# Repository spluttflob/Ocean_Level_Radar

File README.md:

This project aims to create simple and inexpensive designs for measuring 
ocean level from piers, pilings, trees, or other relatively fixed
locations above the water.  THe measurements are to be taken quickly enough
that ocean waves and perhaps wind chop can be resolved. 
Ocean Science Hippies will use these measurements to better understand the 
effects of tides, waves, tsunamis, sea level rise, and other ocean phenomena 
on the coastal environment. 

## Hardware

The custom circuit board design currently used is in `hardware`. 

Mechanical part designs, including radar antennas and lenses, are currently 
being developed and will be added to this repository if and when we figure out
what on Earth we're doing. 

### Power

The current (2026 January) hardware versions may be powered by connecting the
ESP32 to a laptop through a USB cable, **or** by supplying the system with 
5 volts DC through the water resistant connector on the box. 

If a laptop cannot supply enough current through its USB port, the ESP32 may
reboot due to low supply voltage (it says `brownout detected`.)  Usually, 
rebooting a couple of times causes it to come to life; if that doesn't work, 
try another laptop and/or a powered USB hub. 

<span color="red">Only one source of power should be used at a time; **do not** 
connect the ESP32 Feather to a PC while DC power is being supplied through the 
waterproof connector.</span>

## Firmware

The software currently being developed uses a MicroPython program running on an
ESP32 as the overall controller, data logging, and network interface computer.
There is an STM32 microcontroller in the XM125 radar module which runs it own
software which is written in C. 

### ESP32 Firmware

There are two versions of the software which have been developed. The first
version is written in C++, and the second (and currently being worked on) 
version is in MicroPython.

#### C++

The C++ ESP32 firmware is in the `WaterSense_Radar_JJH` directory. 
After cloning this repository, open the `WaterSense_Radar_JJH` directory in a
VSCode/PlatformIO workspace and you should be able to compile and run the
ESP32 firmware. It requires custom firmware to be running on the STM32 in
the XM125 module.

#### MicroPython

For rapid development and testing, MicroPython firmware is provided in the
`MicroPython` folder.  MicroPython for the ESP32 can be downloaded from:  
<https://micropython.org/download/ESP32_GENERIC/>  
The latest release of the `ESP32_GENERIC` software is recommended for our
Feather circuit boards. 

With MicroPython installed on the ESP32, all the Python source files should 
be copied to the root directory of the ESP32's MicroPython filesystem, and 
`radar.cfg` should be copied to the root directory of the ESP32 file
system. Configuration of the system for use at specific sites may require 
editing of `main.py` and `task_mqtt.py`. The main Python file is edited to 
disable unneeded tasks; for example, the MQTT task should be turned off 
(just comment out the `asyncio.create_task()` line) at sites where WiFi 
access and AC power are not available. The radar's range, frequency of data 
collection, and similar configurations are set in `radar.cfg`. 

##### MicroPython File List

The following files need to be uploaded to the root directory of the ESP32's
MicroPython filesystem:

* `as_GPS.py` -- The asyncio GPS file from 
  <https://github.com/peterhinch/micropython-async/tree/master>
  or use the older, unmaintained copy here.
  
* `as_xm125_distance.py` -- From this repository.

* `main.py` -- From this repository.

* `mqtt_as.py` -- The asyncio MQTT client from
  <https://github.com/peterhinch/micropython-mqtt>
  or use the older, unmaintained copy here

* `pcf8523.py` -- Driver for the PCF8523 real-time clock on the Adalogger.
  Modified from others' work; use the copy here.
  
* `queue.py` -- From the standard MicroPython queues at 
  <https://github.com/peterhinch/micropython-async/tree/master>
  again, with an old local copy here for convenience.

* `task_gps.py` -- GPS task file from this repository.

* `task_mqtt.py` -- MQTT task (used if you have AC and WiFi) from this repository.

* `task_sd_card.py` -- SD card task from this repository.

* `radar.cfg` -- The configuration file for each site, put on the SD card.

#### Configuration with `radar.cfg`

The configuration file is a regular text file saved on the data logging SD card.
A typical configuration file might look as follows (for 2025-Dec version of the 
software; configurations are expected to change as the software is improved):
```txt
# Configuration file for Bogan Radar

Site Name:           My_Bench   # Name of site; should be one word (no spaces)
Beginning Distance:  2.0        # Beginning distance (m)
Ending Distance:     8.0        # Ending distance (m)
Sensitivity:         500        # Peak threshold sensitivity
Time Per Point:      5.0        # Time between data points (seconds)
Awake Time:          0.0        # Time taking data, sec., or 0.0 for always awake
Cycle Time:          0.0        # Total on-off cycle time, or 0.0 for always awake
```

_With changes to the value of `SD_DIR` in `task_sd_card.py`, the configuration
file could be saved in the ESP32's built-in flash; this would make reconfiguration 
a little harder but protect the configuration from SD card corruption due to power 
loss, somebody hot swapping the card (bad idea), etc._

If data is sent through MQTT, the MQTT topic is made by appending the site name
from the configuration file to `bogan_radar/`. 

### STM32 on XM125 Firmware

The STM32 microcontroller on the XM125 radar can be given a custom program to
optimize the radar module for our use. We have two setups available:

* When using the MicroPython firmware on the ESP32, the XM125's STM32 must be
  flashed with Acconeer's standard distance measurement application.
  The Acconeer software is available from:  
  <https://developer.acconeer.com/home/a121-docs-software/xm125-xe125/>  
  (You have to enroll with a developer account, but at least it's free to do 
  so.)

* When using the C++ firmware from directory `WaterSense_Radar_JJH` for the 
  ESP32, the source code for the STM32 microcontroller in the XM125 radar 
  module from subdirectory `xm125` must be compiled and flashed to the XM125.
  Compiling the XM125 STM32 code is a bit of a hassle, so we can use a binary 
  copy of the last working code.
  
* It's convenient to use an ST-Link2 programmer to flash the STM32 code to the 
  radar module. There is an ST-Link2 compatible 6-pin programming header near
  the screw terminal on the main circuit board, and there are two pushbuttons
  on the board to reset the STM32 and to put the STM32 in bootloader mode if 
  needed. 

## PC Software

### The _Acconeer Exploration Tool_

This handy application consists of a firmware package and a PC application.
Although it's designed to be run on an official Acconeer development board, the
Exploration Tool can also be run on our boards.

Instructions for setting up the STM32 firmware and Python PC software are at
<https://github.com/acconeer/acconeer-python-exploration>.  Follow Acconeer's 
instructions **with the following exceptions:**

* We usually use leftover ST-Link2 programmers (from old STM32 Nucleo&trade; boards) 
  instead of fussing with DFU programming.  The 6-pin ST-Link2 header next to 
  the power and battery connectors is connected directly to the 6-pin `SWD` (CN4) 
  connector on the ST-Link2, matching the ends marked with dots or triangles. 
  The STM32 Cube Programmer&trade; is a convenient way to flash the binary file
  for the firmware to the STM32. 

* To use our boards with the Exploration Tool, first remove the ESP32 Feather 
  board, any FeatherWing accsesory boards, and the GPS module from the main radar 
  circuit board. Leaving the GPS antenna in place, if present, is OK. 
  Then attach a connector (header pins or sockets) to the three-pin header pad
  marked `STM32 UART0` in the area where the GPS board sits.  Connect a USB to
  RS-232 serial adapter to STM32 UART0 pins, remembering the annoying RS-232 
  standard where RXD of one device must connect to TXD of the other. 
  If you're a civil, environmental, or mechanical engineer: Don't forget the 
  ground wire!  `:)`
  The Exploration Tool should now be able to connect to the XM125 as if the
  XM125 were on the official evaluation board. 

<!-- 
* Use ST-Link to load firmware
* Connect USB-Serial to ST's UART
* Set up Exploration Tool on PC
--> 

### Plotting MicroPython Data

If MicroPython is used, data will be saved in a Semicolon And Comma Separated
Variable (`.sacsv`) format. Some simple programs to plot data in this form are
being developed and can be found in the `CPython` directory. 

An older plotting program (look for lower numbers) uses data in a format 
without the date on each reading; this has caused some inconvenience, so newer
data is saved will a full datetime on every reading, and newer CPython scripts
with higher numbers in the file names use the newer format. 

### Plotting C++ Firmware Data

Some more fully Python developed programs to analyze data from the C++ firmware 
are in the `ESP32_to_Python_GUI` directory. 

It is our intention to merge the capabilities of the CPython programs from
the `CPython` and `ESP32_to_Python_GUI` directories to create especially 
convenient and flexible data analysis and plotting applications. 

## References

* A Masters thesis utilizing ultrasonic rather than radar sensors which gives
  some perspective to the project:  
  <https://digitalcommons.calpoly.edu/theses/2745/>

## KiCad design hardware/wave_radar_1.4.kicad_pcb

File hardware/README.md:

# Bogan Radar Hardware Notes

**Version 1.4 (Still in alpha)**

This newer board is simpler and easier to assemble than V1.3.  All the SMD parts
are on one side of the board, so the SMDs can be soldered on first; a hot plate
works pretty well for this.  After the SMDs are in place, the through-hole parts 
can be attached to the other side.  The assembly of the board to the radar
antenna and installation in an enclosure are the same for both boards. 

**Version 1.3 (Obsolete; do not use)**

_**NOTE:** The 1.3 board version has not performed well enough in testing and is
considered obsolete. Newer boards are being prepared. The process of installing
the newer boards will be the same as that of installing older boards._

The current design uses the following bits:

* An Acconeer&trade; XM125 radar mounted to the bottom of a circuit board, with
  headers for many of the XM125 pins broken out to through holes on the board

* An Adalogger&trade; Featherwing for its SD card and battery backed up 
  real-time clock, mounted in a socket atop the board using stacking headers

* An ESP32 Feather board (EZSBC made boards preferred) mounted atop the 
  Adalogger
  
* A generic GPS receiver atop the circuit board

* A LiPo battery charging circuit built into the Feather board

The radar system is enclosed in a generic waterproof junction box. 
The board is mounted atop a horn-type millimeter-wave antenna that is attached
to the box with a waterproof seal.  The system is watertight so that it has a
chance to survive when deployed just above the ocean. 

_Note from testing: The enclosure shown has been tested in and survived 
several rainstorms, though a small amount of water was found in the bottom of
the box after about 6 weeks and several storms._

## Board V1.3 Hacks (legacy; use newer boards)

The design of the system has changed since a batch of the Version 1.3 boards
was manufactured, so there have been some hacks made involving jumper wires.
Please see [HACKS_1.3](HACKS_1.3.md) for details.

## RADAR Antenna

The horn antenna is a simple cylindrical design, manufactured mostly using a
lathe:

There are other antennas available such as plastic lenses. These may work well
also, and antenna testing and comparison are ongoing.

## Mounting in Enclosure

The branding of a typical enclosure is shown below.  This is not an endorsement
of this particular enclosure above others; it's just something we've tried:

The antenna is mounted in the bottom of the box. A 1 inch hole is cut for the
antenna and the antenna is pushed in from the outside. We have had good results
using a step drill to make the hole.  Sealant is applied to
the flat mounting face of the antenna to prevent water ingress, and a couple of 
\#6-32 screws are tapped into the mounting face of the antenna to secure it to 
the box:

A 3D printed board mounting piece is attached to the upper side of the antenna 
to mount the circuit board. The end of the antenna must be flush with the slot
in the face of the board mount, as shown below using a ruler to verify that the
board mount is at the correct height. It's a little hard to see in the photo,
but the edge of the ruler is down in the slot, _not_ up on the faces of the
board mount that contact the board. This is critical because the XM125 sensor
will be in that slot when the board is mounted:

The board attaches to its mount with four annoyingly tiny screws. Ensure that
nobody sneezes to prevent losing the screws.  After the board is mounted, the
Featherwing, ESP32, and GPS can be inserted in their sockets and the electrical
power connection (see below) hooked up. 

The ESP32 Feather and Adalogger boards are stacked onto the Feather connectors
on the board in the usual way. Depending on the type of GPS module used, one
may need to mount the GPS antenna separately from the GPS module board.  If so,
the antenna can be mounted to the area marked `GPS Antenna Pad` on the board
with some double-sided foam tape. 
It is recommended to mount the GPS antenna so that the board mounting screw is
easily accessible with a screwdriver, as the need to remove the board for
updates or repairs is all but guaranteed in a research project. 

## Electrical Power Connection

For most uses, electricity must be supplied to the radar system from outside, 
either a solar panel or 5 volt wall plug adapter. _**Note:** The adapter should
be rated to produce 5.0 to 5.2 volts at around 1 amp. EZSBC boards are
designed to be supplied from 5 volt USB supplies and rated to handle up to 5.5
volts._  The power connection must be watertight.  In an experimental setup, we
have used an inexpensive waterproof automotive style connector glued into a hole
in the side of the box. 

## Radar Antenna Cover

This is an area of ongoing research. The radar may have an optimally tight beam
if a plastic phase corrector is attached across the bottom (wide) opening of
the horn antenna, but for initial testing we're trying polypropylene and
polyethylene disks made from various containers. The cover's ideal width which 
minimizes reflections of the 60GHz signal depends on the material used. 
The Interwebs seem to say that a 1.5mm (about 1/16") sheet of polypropylene 
would make a good cover. Disks of UHMW polyethylene (we think) cut from a
Tupperware&trade; bowl lid saved from a dumpster seem to work pretty well too.
More will be posted when we have conducted more experiments. 

Remember that the cover must be attached to the end of the horn with a 
watertight connection to protect the sensor from rain, waves, spray, and
errant organisms. A version of the aluminum horn antenna which has a threaded
end, combined with a threaded PVC ring that holds a cover firmly against the
end of the antenna, seems to work well.  We may use a bit of caulk or pipe
dope to ensure a good seal.

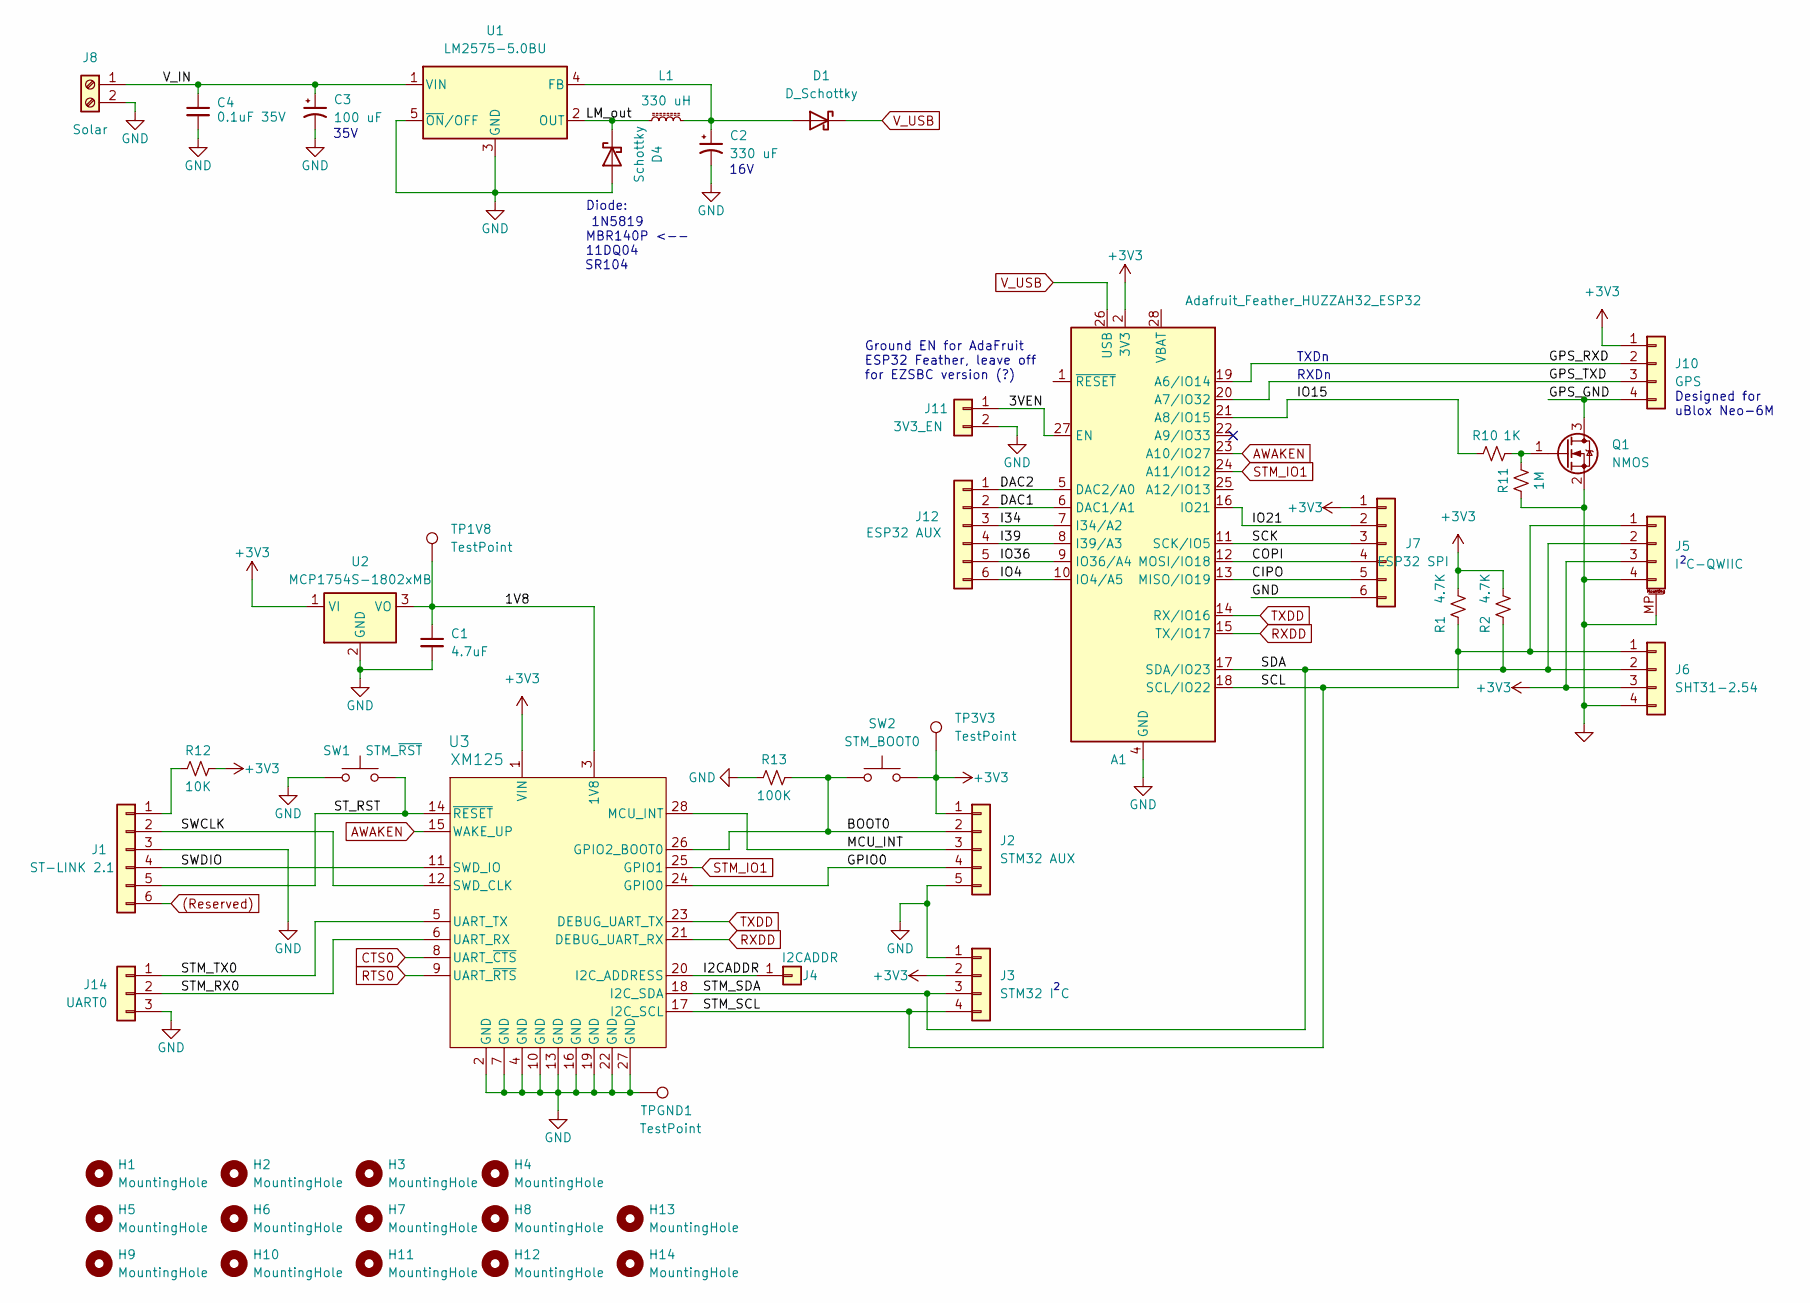
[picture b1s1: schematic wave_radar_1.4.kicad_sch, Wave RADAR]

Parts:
A1: Adafruit_Feather_HUZZAH32_ESP32; Adafruit_Feather
C1: 4.7uF; C_0805_2012Metric
C2: 330 uF; CP_Radial_D8.0mm_P3.50mm
C3: 100 uF; CP_Radial_D8.0mm_P3.50mm
C4: 0.1uF 35V; C_0805_2012Metric
D1: D_Schottky; D_1206_3216Metric
D4: Schottky; D_1206_3216Metric
H1, H2, H3, H4, H5, H6, H7, H8, H9, H10, H11, H12, H13, H14: MountingHole; MountingHole_2.7mm
J1: ST-LINK 2.1; PinHeader_1x06_P2.54mm_Vertical
J2: STM32 AUX; PinHeader_1x05_P2.54mm_Vertical
J3: STM32 I C; PinHeader_1x04_P2.54mm_Vertical
J4: I2CADDR; PinHeader_1x01_P2.54mm_Vertical
J5: I C-QWIIC; JST_SH_BM04B-SRSS-TB_1x04-1MP_P1.00mm_Vertical
J6: SHT31-2.54; PinHeader_1x04_P2.54mm_Vertical
J7: ESP32 SPI; PinHeader_1x06_P2.54mm_Vertical
J8: Solar; TerminalBlock_Phoenix_MPT-0,5-2-2.54_1x02_P2.54mm_Horizontal
J10: GPS; PinSocket_1x04_P2.54mm_Vertical
J11: 3V3_EN; PinHeader_1x02_P2.54mm_Vertical
J12: ESP32 AUX; PinHeader_1x06_P2.54mm_Vertical
J14: UART0; PinHeader_1x03_P2.54mm_Vertical
L1: 330 uH; Inductors for LM2575, Pulse PE-xxxxx
Q1: NMOS; SOT-23
R1, R2: 4.7K; R_0805_2012Metric
R10: 1K; R_0805_2012Metric
R11: 1M; R_0805_2012Metric
R12: 10K; R_0805_2012Metric
R13: 100K; R_0805_2012Metric
SW1: STM_~{RST}; SW_PUSH_1P1T_6x3.5mm_H4.3_APEM_MJTP1243
SW2: STM_BOOT0; SW_PUSH_1P1T_6x3.5mm_H4.3_APEM_MJTP1243
TP1V8, TP3V3: TestPoint; TestPoint_Loop_D2.50mm_Drill1.0mm
TPGND1: TestPoint; TestPoint_Loop_D2.50mm_Drill1.0mm
U1: LM2575-5.0BU; TO-263-5_TabPin3
U2: MCP1754S-1802xMB; SOT-223-3_TabPin2
U3: XM125; XM125_ACC

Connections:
(Reserved): J1.6
+3V3: A1.2 (3V3), J2.1, J3.2, J5.3, J6.3, J7.1, J10.1, R1.2, R2.2, R12.2, SW2.2, TP3V3.1, U2.1 (VI), U3.1 (VIN)
/1V8: C1.1, TP1V8.1, U2.3 (VO), U3.3 (1V8)
/3VEN: A1.27 (EN), J11.1
/BOOT0: J2.2, R13.2, SW2.1, U3.26 (GPIO2_BOOT0)
/CIPO: A1.13 (MISO/IO19), J7.5
/COPI: A1.12 (MOSI/IO18), J7.4
/DAC1: A1.6 (DAC1/A1), J12.2
/DAC2: A1.5 (DAC2/A0), J12.1
/GPIO0: J2.4, U3.24 (GPIO0)
/GPS_GND: J10.4, Q1.3 (D)
/GPS_RXD: A1.19 (A6/IO14), J10.2
/GPS_TXD: A1.20 (A7/IO32), J10.3
/I2CADDR: J4.1, U3.20 (I2C_ADDRESS)
/I34: A1.7 (I34/A2), J12.3
/I39: A1.8 (I39/A3), J12.4
/IO4: A1.10 (IO4/A5), J12.6
/IO15: A1.21 (A8/IO15), R10.1
/IO21: A1.16 (IO21), J7.2
/IO36: A1.9 (IO36/A4), J12.5
/LM_out: D4.1 (K), L1.1, U1.2 (OUT)
/MCU_INT: J2.3, U3.28 (MCU_INT)
/SCK: A1.11 (SCK/IO5), J7.3
/SCL: A1.18 (SCL/IO22), J3.4, J5.1, J6.1, R1.1, U3.17 (I2C_SCL)
/SDA: A1.17 (SDA/IO23), J3.3, J5.2, J6.2, R2.1, U3.18 (I2C_SDA)
/STM_RX0: J14.2, U3.6 (UART_RX)
/STM_TX0: J14.1, U3.5 (UART_TX)
/ST_RST: J1.5, SW1.1, U3.14 (~RESET)
/SWCLK: J1.2, U3.12 (SWD_CLK)
/SWDIO: J1.4, U3.11 (SWD_IO)
/V_IN: C3.1, C4.1, J8.1, U1.1 (VIN)
AWAKEN: A1.23 (A10/IO27), U3.15 (WAKE_UP)
CTS0: U3.8 (UART_~CTS)
GND: A1.4 (GND), C1.2, C2.2, C3.2, C4.2, D4.2 (A), J1.3, J2.5, J3.1, J5.4, J5.MP (MountPin), J6.4, J7.6, J8.2, J11.2, J14.3, Q1.2 (S), R11.1, R13.1, SW1.2, TPGND1.1, U1.3 (GND), U1.5 (~ON/OFF), U2.2 (GND), U3.2 (GND), U3.4 (GND), U3.7 (GND), U3.10 (GND), U3.13 (GND), U3.16 (GND), U3.19 (GND), U3.22 (GND), U3.27 (GND)
unnamed: C2.1, D1.2 (A), L1.2, U1.4 (FB)
unnamed: J1.1, R12.1
unnamed: Q1.1 (G), R10.2, R11.2
RTS0: U3.9 (UART_~RTS)
RXDD: A1.15 (TX/IO17), U3.21 (DEBUG_UART_RX)
STM_IO1: A1.24 (A11/IO12), U3.25 (GPIO1)
TXDD: A1.14 (RX/IO16), U3.23 (DEBUG_UART_TX)
V_USB: A1.26 (USB), D1.1 (K)

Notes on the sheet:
SR104
1N5819
35V
Ground EN for AdaFruit ESP32 Feather, leave off for EZSBC version (?)
MBR140P <--
11DQ04
RXDn
16V
Diode:
Designed for uBlox Neo-6M
TXDn

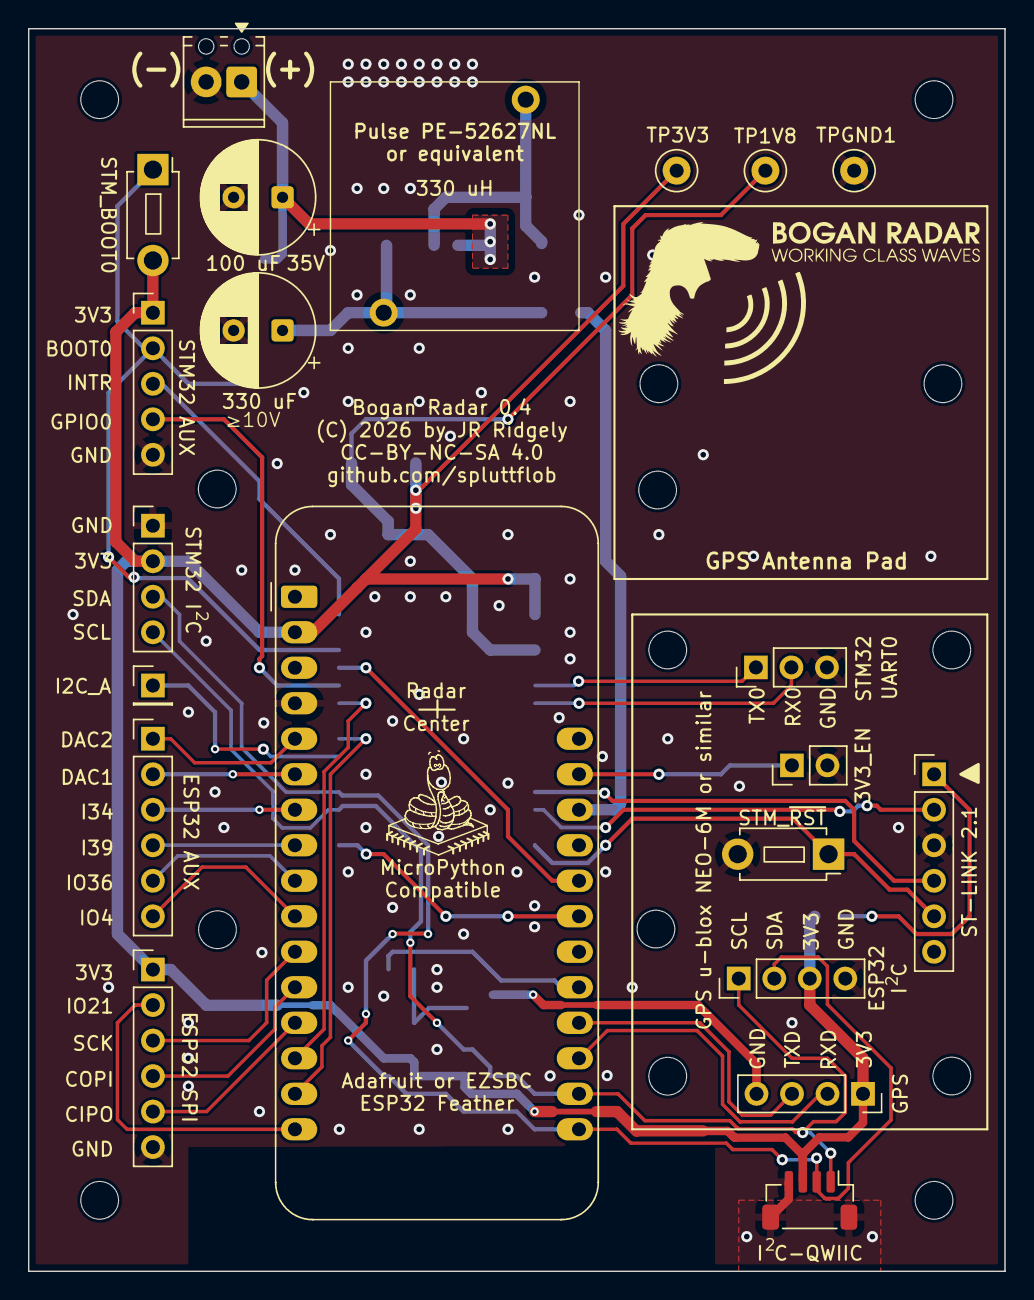
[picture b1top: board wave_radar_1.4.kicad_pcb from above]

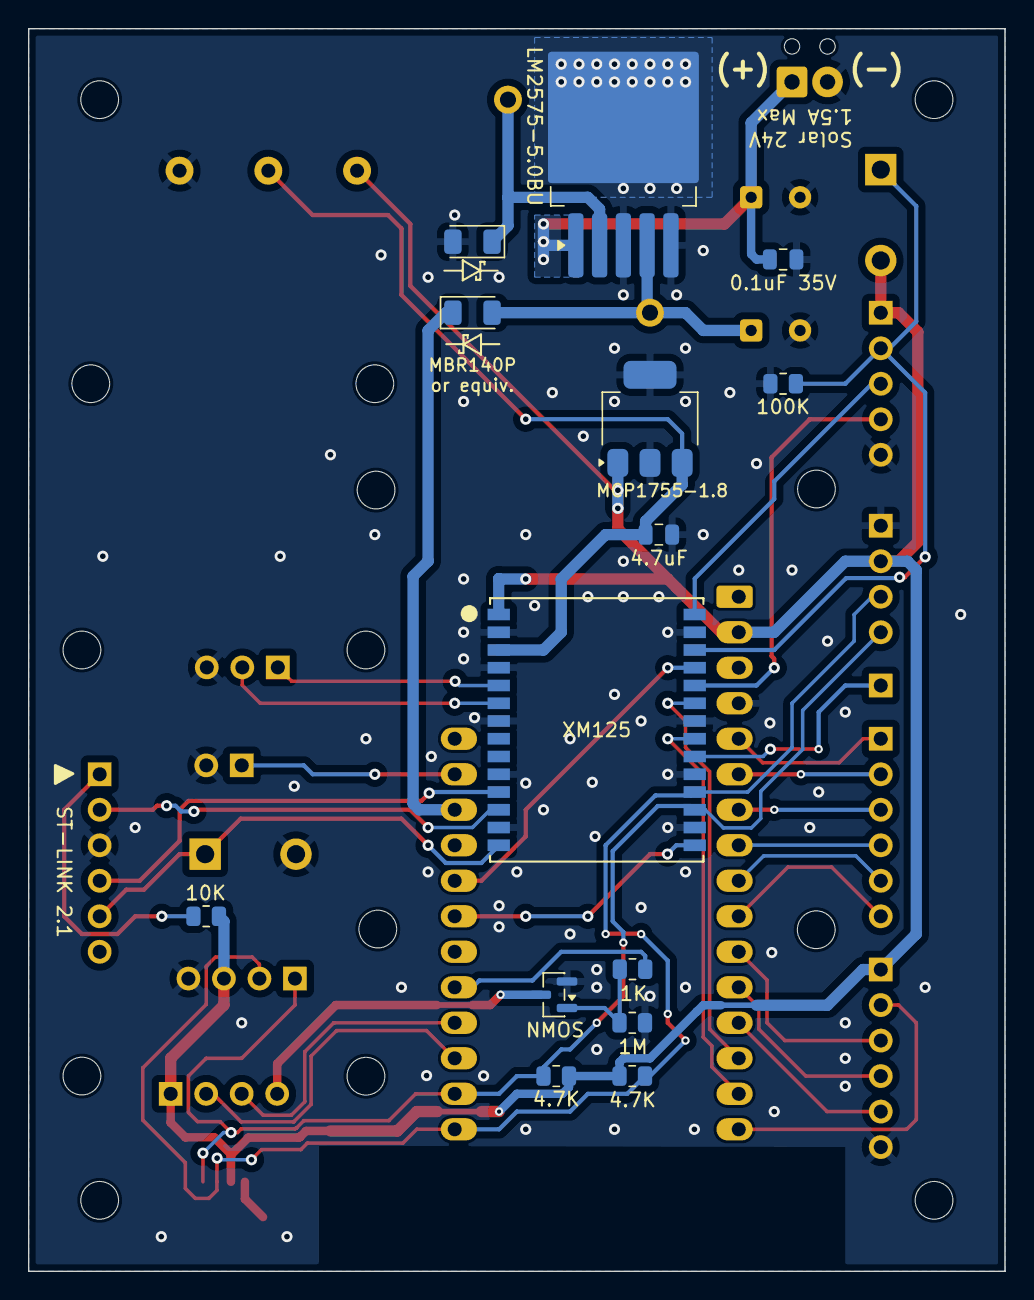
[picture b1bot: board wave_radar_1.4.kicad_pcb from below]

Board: 2 copper layers, 69.8 x 88.9 mm, 49 parts (14 on the bottom side), 39 nets.

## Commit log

2025-11-08 Rearranged directories and began README
2025-11-08 Added custom PCB designs to hardware/
2025-11-08 More progress on README and fixed too-specific setup in platformio.ini
2025-11-09 Added drawing of first try horn antenna, more README updates
2025-11-29 Got basic MicroPython firmware running; removed XM125 stuff
    We're using the stock XM125 applications with the MicroPython firmware, so a custom XM125 program isn't needed at this time.
2025-12-02 Improved READMEs with photos, updates to MicroPython programs
2025-12-02 Show board mounting area on hack_bottom_xz.jpg
2025-12-03 Refactorficationized and de-obfuscated README.md (somewhat)
2025-12-03 Added CPython programs that display data from MicroPython based radar
2025-12-07 Trying to have task_mqtt() queue messages for sending in a bunch...not great
2025-12-09 Moved bunching of data for MQTT to main.py instead of task_mqtt.py
2025-12-12 Minor cleanup, preparing for first deployment
2025-12-13 README updates, moved objects
    The SD card, GPS, and UART objects are moved to files for the tasks which use them.
    GPS pins are changed (seemed to be wrong ones?) and a bug fixed where the GPS TXD (ESP32 RXD) pin was configured by MicroPython in a way that prevented reliable GPS data transmission.
    MQTT topic name is configured using the configuration file site name.
2025-12-13 Added file list to main README; added some ignorance
2025-12-13 Added project logo to README
2025-12-15 Added CPython program to plot tide height from data files with full datetime
2025-12-16 Added software watchdog and split watchdog.py contents
2025-12-18 Better timing for main.py; added web file server
    Added 'periodic' timing to prevent clock drift in measurements.
    Added web server usable for downloading data files from SD card.
    Minor changes to support the above.
2025-12-20 Added wavefft.py, a non-uniform FFT program mostly by AI
2026-01-01 Working on out-of-memory errors, not done
2026-01-01 Updated wavefft1, added databatch.py, added waverad1.py (new version)
2026-01-04 In progress: databatch single buffered, task_mqtt, new task_network.py
2026-01-12 Updating most Python to try to fix memory leaks, not done yet
2026-01-15 Newer mqtt_as working; use some .mpy to save memory
    This version has passed a half-day test with the watchdog timer running, etc. using MQTT to a local server (192.168.x.x). Still needs testing to cloud, at the water, etc.
2026-01-24 Partway through updates to SD and MQTT
    Don't use this version, as work is in progress on changing how data is transferred from the radar to the SD card and MQTT.
2026-01-25 Added testq.py with a GPT created 1-put, many-get queue-like thing.
2026-01-26 Fixed broadcast queue; changed to bytes
    Changed as_xm_125_distance.py to emit bytearrays, not Unicode strings; added broadqueue.py with a broadcast queue class; changed databatch.py t use broadqueue.py; modified task_mqtt.py to use the new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
2026-01-28 Field testable version with new DataBatch and watchdog
    The new databatch is now in full use.
    The watchdog now awaits events from watched tasks.
    Has been tested and found to run OK for a few hours; needs much more testing.
2026-01-28 Update README with note on board version obsolescence
    Added note about the obsolescence of version 1.3 and upcoming boards.
2026-01-29 New README, bug fix in task_gps, moved *.mpy files
    Fixed bug where task_gps.py wasn't putting data in the batch because author forgot to await the put.
    Added README for MicroPython directory showing what files are needed for system to run.
    Put the *.mpy files in a subdirectory to prevent excessive messiness.
2026-01-30 Made a worflow YAML file for .mpy files
    A first attempt at setting up a workflow to compile all the .py files into .mpy files.
2026-01-30 Fixed a bug in build-mpy.yaml
2026-01-30 Minor change to broadqueue.py
    ...to test .mpy workflow.
2026-01-30 Removed pip caching from YAML
    The workflow keeps failing...
2026-01-30 Still trying to get workflow working
2026-01-30 Still trying to fix worflow
2026-01-30 Added manual workflow trigger, maybe?
2026-01-30 Fixed another workflow bug...
2026-01-30 Auto-generate .mpy files
2026-06-02 Added version 1.4 of circuit board; modified README (partly) to explain this

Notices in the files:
hardware/wave_radar_1.4.kicad_pcb:
(C) 2026 by JR Ridgely
CC-BY-NC-SA 4.0
